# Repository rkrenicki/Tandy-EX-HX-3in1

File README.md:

# Tandy 1000 EX/HX 3-in-1 Expansion Board

This is a single expansion board designed for the Tandy 1000 EX and HX computers, to include the following upgrades:

* 640KB Base System Memory
* 96KB Upper Memory
* 16550-based DE9 Serial RS232 Port
* XT-IDE based CompactFlash "Hard Drive"

## Prerequisites

This board is for the Tandy 1000EX and 1000HX computers only.  It will not work in any other computer model as it is.
You must remove any expansion cards already in the computer, this is designed to be a single-board upgrade and has no provisions to allow for any other expansion cards.

## Installing

This board plugs into the Tandy PLUS interface, and takes up "Slot 2" on the rear of the computer.  Please be careful to align the PLUS bus connector before pushing down, to avoid bending pins on the computer.  Secure the backplate to the computer with two screws.
The IDE BIOS will automatically start and boot directly to the CF card on 1000EX machines.   1000HX loads a boot menu by default, and you will need to press F4 to load the IDE BIOS.  If you want to bypass the Tandy DOS ROM and boot menu, run "SETUPHX" and change the "Primary Start-up Device" to "DISK" and press F1 to save.

## Technical Details

This board has no configuration jumpers and is designed to be plug-and-play.  The only jumper is to enable programming the ROM.  Install the jumper to flash the XT-IDE BIOS, otherwise the jumper should be removed.  All assembled boards and kits sold by me come with a pre-programmed ROM, and this jumper should be left empty.

The board is hardwired with these memory locations/ports:
```
SRAM:  0x0000-0x5FFF, 0xC800-0xDFFF
UART:  0x3F8, IRQ 4
IDE:   0x300
ROM:   0xC000-0xC7FF
```

## Assembly Notes
All functions of the board are independent, no parts are shared between functions.  If you do not want to use a specific function, you can safely omit any parts referenced with the function in the name (such as "232" for RS232).

Recommended assembly order: (Shortest to tallest)
* 1  - Resistors (R1-R3, R4 for v1.8+)
* 2  - Bypass Capacitors (C1-C16, only noted as "0.1uF" on the boards)
* 3  - 74 series Chips (U1-4, U6-7, U9, U11-13)
* 4  - ROM Socket (U5 Socket)
* 5  - SRAM Chip (U10)
* 6  - Oscillator (OSC1)
* 7  - UART Socket (U8 Socket)  - Pay very special attention to the orientation!  See note below.
* 8  - Connectors (BUS1, CF-J1, CF-J2, 232-P2)
* 9 -  ROM and UART chips into their sockets.
* 10 - CF Adapter 
* 11 - Backplate 

NOTE:  Please take careful note of part orientation.  To optimize some trace routing, not all chips are oriented in the same direction.  232-U6, 232-U8, and RAM-U11 are all opposite oritentation than the other horizontal chips.  Installing these backwards will destroy the chips.   Pay special attention to 232-U8's socket, it must be installed with the "Pin 1 Arrow" installed facing towards the left of the board.  232-OSC1 is installed "upside down", with the squared corner facing the upper right.

## Bill of Materials
|Quantity |Ref(s)        |Mouser Part Number  |Digikey Part Number |Description                                                     
|-----|--------------|--------------------|--------------------|----------------------------------------------------------------
| 1   |BUS1          |200-CES13101SD<br><i><b>See Note2 Below</i>|SAM1084-31-ND<br><i><b>See Note2 Below</i>|2x31 2.54mm Header Socket
| 1   |CF-J1         |517-8540-4500PL     |MSPV40-ND               |2x20 2.54mm Header Socket, 11mm height.
| 4   |R1 through R4 |603-CFR-12JT-52-10K |13-CFR-12JT-52-10KCT-ND |10kOhm Resistor, 1/10w or 1/8w
| 16  |C1 through C16|594-K104M15X7RF53L2 |BC5142-ND               |0.1uF Multilayer Ceramic Capacitor, 2.5mm Lead Spacing
| 1   |CP1           |647-RNU1C101MDS1    |493-16276-ND            |47-100uF 6.3-16V Polymer or Electrolytic Capacitor, 2.5mm Lead Spacing
| 1   |232-OSC1      |774-MXO45HS-3C-1.8  |110-MXO45HS-3C-1M843200-ND |1.8432Mhz 1/2-size Oscillator
| 1   |232-P2        |806-K22X-E9P-N-99   |2092-K22X-E9P-N-ND      |DE9 Male Right Angle Connector  
| 2   |232-P2 Screw  |571-5207953-3       |SFSO4401NR-ND           |Jackscrew for DE9 connector
| 1   |232-U6        |595-GD75232N        |296-GD75232N-ND         |GD75232N RS232 Driver
| 2   |232-U7, 232-U9|595-SN74LS138N      |296-1639-5-ND           |74LS138 3-to-8 Line Demux
| 1   |232-U8        |701-ST16C550CJ44TR-F|1016-1259-5-ND          |16550/16C550 UART in PLCC-44 Package 
| 1   |232-U8 Socket |517-8444-11B1-RK-TP |3M4411B1-ND             |PLCC-44 Through Hole Socket
| 1   |CF-J2         |200-CES10101TD      |SAM1086-01-ND           |1x2 2.54mm Header Socket
| 1   |CF-U1         |595-SN74LS139AN     |296-1640-5-ND           |74LS139 Dual 2-to-4 Demux
| 2   |CF-U2, ROM-U4 |595-SN74LS688N<br> or 595-SN74F521N|296-1667-5-ND|74LS688 or 74F521 8-bit Comparator
| 2   |CF-U3, RAM-U11|595-SN74LS245N      |296-1655-5-ND           |74LS245 Tri-state Bus Transciever
| 1   |RAM-U10       |913-AS6C4008-55PCN  |1450-1027-ND            |AS6C4008-55PCN 4mbit (512k x 8) Static RAM
| 1   |RAM-U12       |595-SN74LS00N       |296-1626-ND             |74LS00 Quad NAND Gate
| 1   |RAM-U13       |595-SN74LS32N       |296-1658-5-ND           |74LS32 Quad OR Gate
| 1   |ROM-U5        |556-AT28C64B15PU    |AT28C64B-15PU-ND        |28C64 64k x 8 EEPROM
| 1   |ROM-U5 Socket |517-4828-6000-CP    |ED3052-5-ND             |28-pin Wide DIP Socket
| 1   |CF-IDE Adapter|n/a                 |n/a                     |CF to IDE Adapter from eBay or AliExpress (See note below)
| 1   |J1            |534-7327            |36-7327-ND              |Mounting Tab for Backplate

Note:	All 74LSxx series logic ICs can be substituted with any family with "LS" or "T" in the name, such as ALS, ACT, AHCT, or HCT among others.

Note2: For the BUS1 Connectors, I have many of these left over from my last order of custom connectors.   You can buy them from me for $1/ea plus shipping.  Even for one, it is far cheaper than the $13 that Mouser wants.   
For small quantities (1-20 connectors), visit my Tindie store to order:  https://www.tindie.com/products/rkrenicki/tandy-1000-ex-and-hx-bus-connector/
For larger quantities, please email tandy.3in1@gmail.com.
## BIOS

This board uses the XT-IDE Universal BIOS.  I have included pre-configured images for 2.0.0B3 r602 (latest version as of the time of writing this).  The 3in1BIOS-8088.zip will work on any EX or HX computer, and is the version that I preload on assembled boards and kits.   I have also included a V20 Enhanced version for any EX/HX that has an NEC V20 (or clone) installed.   This enhanced version will roughly double your disk speed, but only works on V20 machines.

## CF-IDE Adapter

This board is designed a specific version of a CF-IDE adapter.  They are widely available on eBay and AliExpress.  It bears the mark of "IDE to CF Ver.D2".  It can generally be identified by the metal cover over the CF card connector.   I do not have a link to any one specific vendor or listing, but if the adapter includes the metal backplate and has a metal cover over the CF slot, then it should be correct. 

The CF adapter does also need a few modifications, please refer to "PDFs\IDE Adapter Modifications.pdf" for details.  It also has photos of the adapter for reference to buy the proper adapter.  The backplate also has provisions for a mounting tab, please follow the directions found in "PDFs\Backplate Directions.pdf"

If you have any questions, feel free to join the Discord server below and ask in the #tandy-3in1-support channel.

## Support Discord

I have started a Discord server for more real-time technical support, as well as discussion for my various projects in progress.   You can follow this link to join:  https://discord.gg/QmFssyXnQt

## Built With

* [KiCAD EDA](http://www.kicad.org/)

## Authors

* **Rob Krenicki** - [rkrenicki](https://github.com/rkrenicki)

## License

This project is licensed under the Creative Commons - Attribution - ShareAlike 3.0 License

## Attribution

This board was derrived from works by, uses design elements from, or contains sofware writen by the following:
* Sergey Kiselev (http://www.malinov.com/Home/sergeys-projects)
* James Pearce (https://www.lo-tech.co.uk/)
* Adrian Black (https://www.youtube.com/user/craig1black/featured)
* Jacob Dorne of Monotech PCs (https://monotech.fwscart.com/)
* XTIDE Universal BIOS Team (http://www.xtideuniversalbios.org/)

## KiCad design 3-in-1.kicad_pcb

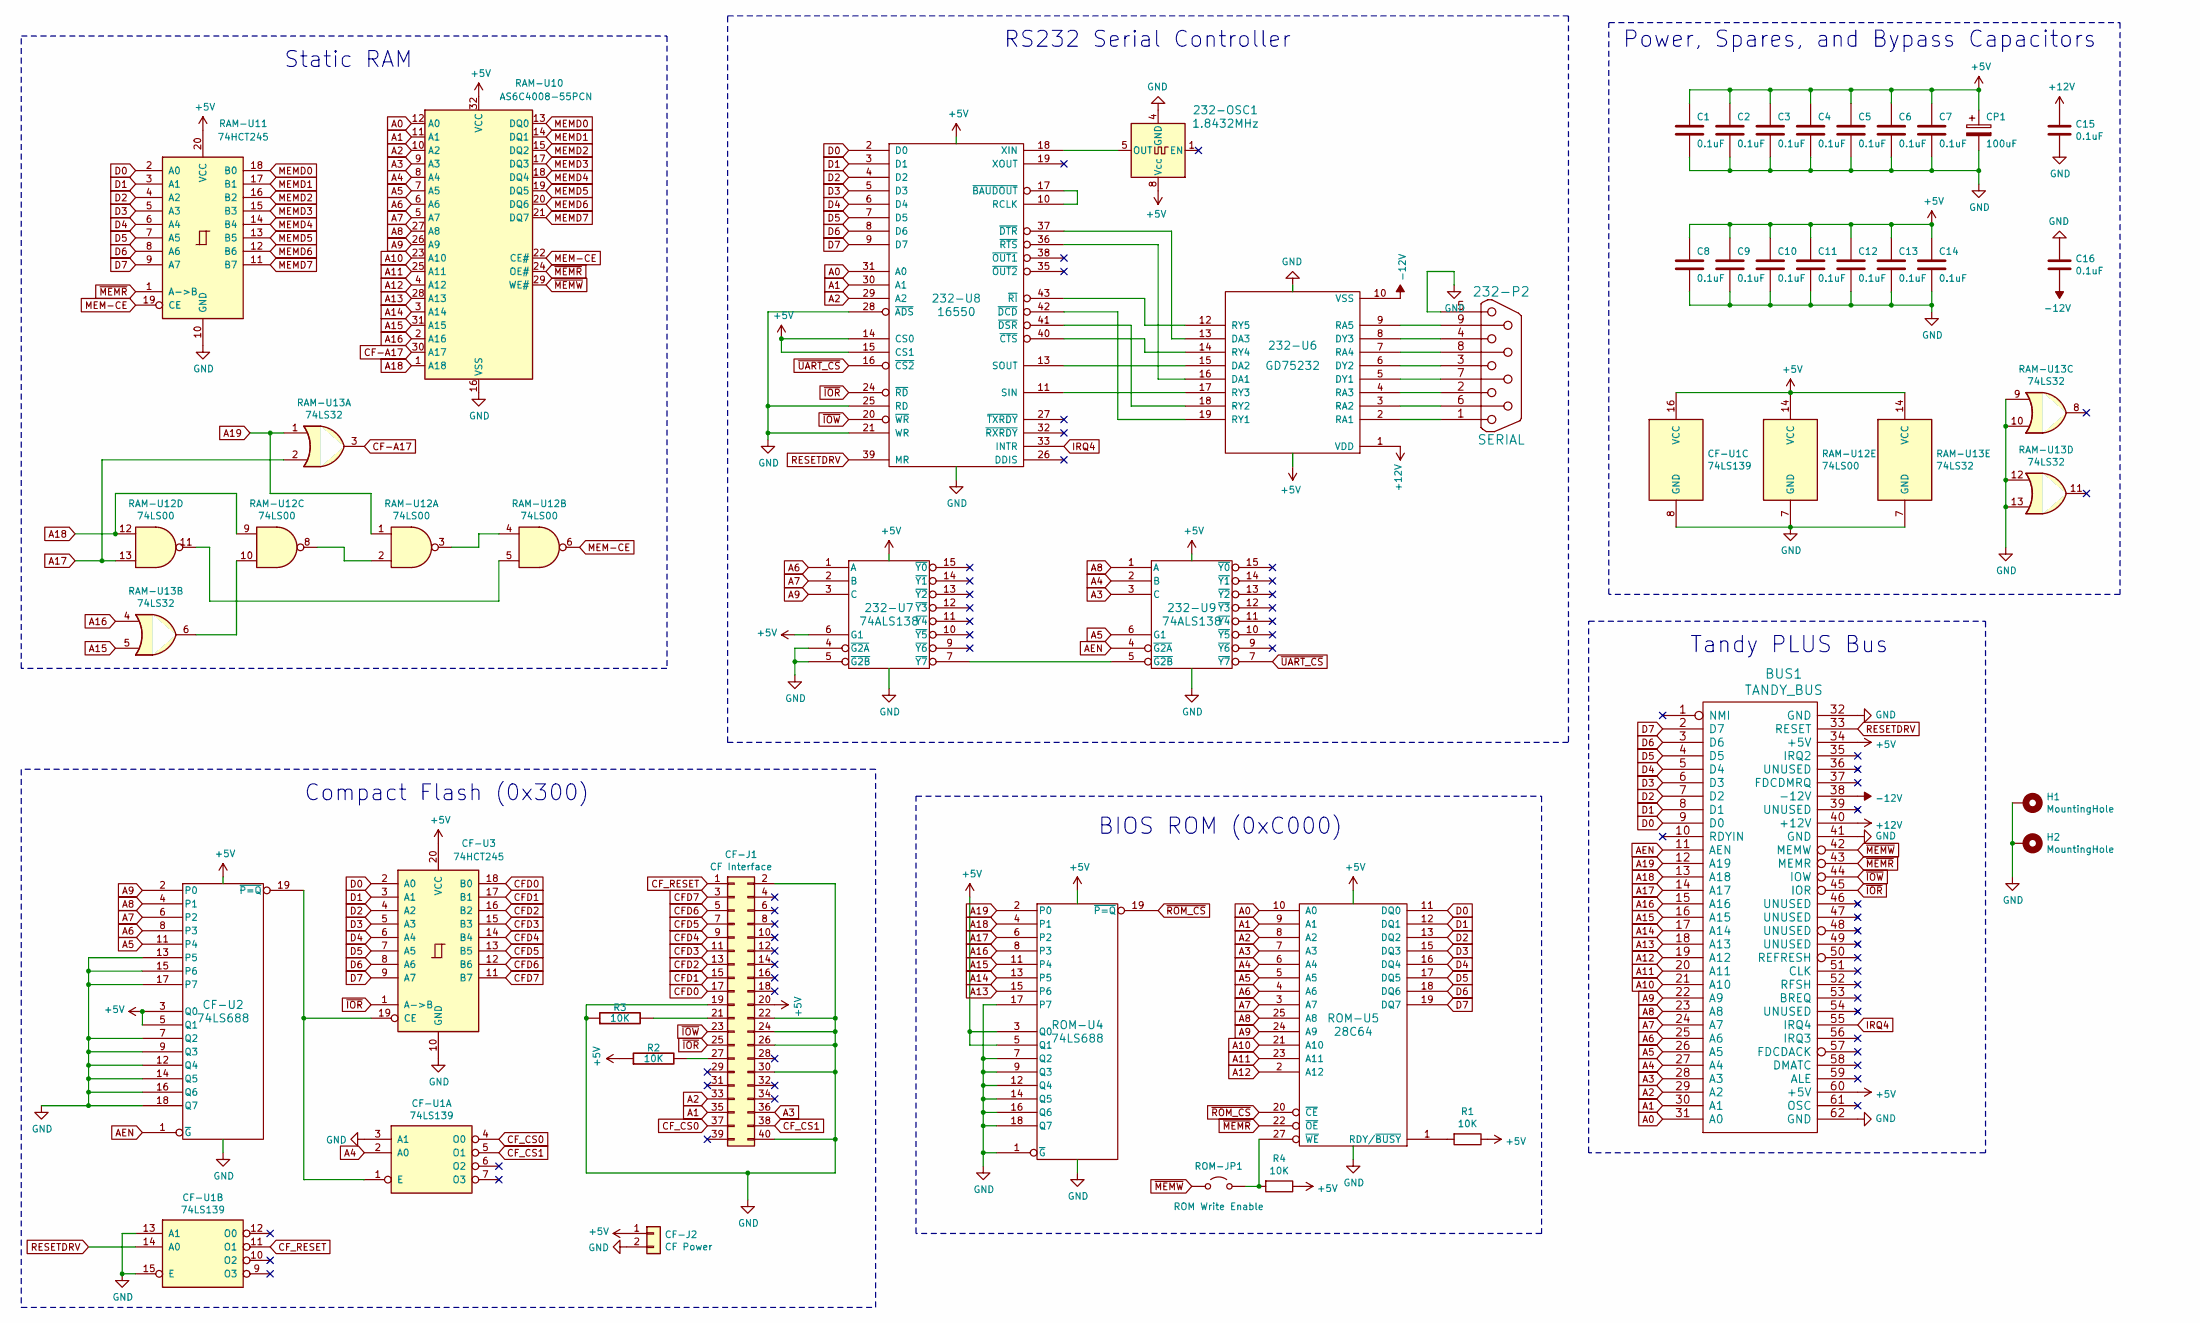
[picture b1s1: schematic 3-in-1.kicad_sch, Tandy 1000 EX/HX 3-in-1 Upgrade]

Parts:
232-OSC1: 1.8432MHz; Oscillator_DIP-8
232-P2: SERIAL; DSUB-9_Male_Horizontal_P2.77x2.84mm_EdgePinOffset7.70mm_Hou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
232-U6: GD75232; DIP-20_W7.62mm
232-U7, 232-U9: 74ALS138; DIP-16_W7.62mm
232-U8: 16550; PLCC-44_THT-Socket
BUS1: TANDY_BUS; TANDY-PLUS-BUS
C1, C2, C3, C4, C5, C6, C7, C8, C9, C10, C11, C12, C13, C14, C15, C16: 0.1uF; C_Disc_D3.0mm_W2.0mm_P2.50mm
CF-J1: CF Interface; PinSocket_2x20_P2.54mm_Vertical
CF-J2: CF Power; PinSocket_1x02_P2.54mm_Vertical
CF-U1: 74LS139; DIP-16_W7.62mm
CF-U2: 74LS688; DIP-20_W7.62mm
CF-U3: 74HCT245; DIP-20_W7.62mm
CP1: 100uF; CP_Radial_D5.0mm_P2.50mm
H1, H2: MountingHole; MountingHole_2.7mm_M2.5_ISO7380_Pad
R1, R2, R3, R4: 10K; R_Axial_DIN0204_L3.6mm_D1.6mm_P5.08mm_Horizontal
RAM-U10: AS6C4008-55PCN; DIP-32_W15.24mm
RAM-U11: 74HCT245; DIP-20_W7.62mm
RAM-U12: 74LS00; DIP-14_W7.62mm
RAM-U13: 74LS32; DIP-14_W7.62mm
ROM-JP1: ROM Write Enable; PinHeader_1x02_P2.54mm_Vertical
ROM-U4: 74LS688; DIP-20_W7.62mm
ROM-U5: 28C64; DIP-28_W15.24mm

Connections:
+5V: 232-OSC1.8 (Vcc), 232-U6.20 (VCC), 232-U7.6 (G1), 232-U7.16 (VCC), 232-U8.14 (CS0), 232-U8.15 (CS1), 232-U8.44 (VCC), 232-U9.16 (VCC), BUS1.34 (+5V), BUS1.60 (+5V), C1.1, C2.1, C3.1, C4.1, C5.1, C6.1, C7.1, C8.1, C9.1, C10.1, C11.1, C12.1, C13.1, C14.1, CF-J1.20, CF-J2.1, CF-U1.16 (VCC), CF-U2.3 (Q0), CF-U2.5 (Q1), CF-U2.20 (VCC), CF-U3.20 (VCC), CP1.1, R1.1, R2.1, R4.1, RAM-U10.32 (VCC), RAM-U11.20 (VCC), RAM-U12.14 (VCC), RAM-U13.14 (VCC), ROM-U4.3 (Q0), ROM-U4.5 (Q1), ROM-U4.20 (VCC), ROM-U5.28 (VCC)
+12V: 232-U6.1 (VDD), BUS1.40 (+12V), C15.1
-12V: 232-U6.10 (VSS), BUS1.38 (-12V), C16.2
A0: 232-U8.31 (A0), BUS1.31 (A0), RAM-U10.12 (A0), ROM-U5.10 (A0)
A1: 232-U8.30 (A1), BUS1.30 (A1), CF-J1.35, RAM-U10.11 (A1), ROM-U5.9 (A1)
A2: 232-U8.29 (A2), BUS1.29 (A2), CF-J1.33, RAM-U10.10 (A2), ROM-U5.8 (A2)
A3: 232-U9.3 (C), BUS1.28 (A3), CF-J1.36, RAM-U10.9 (A3), ROM-U5.7 (A3)
A4: 232-U9.2 (B), BUS1.27 (A4), CF-U1.2 (A0), RAM-U10.8 (A4), ROM-U5.6 (A4)
A5: 232-U9.6 (G1), BUS1.26 (A5), CF-U2.11 (P4), RAM-U10.7 (A5), ROM-U5.5 (A5)
A6: 232-U7.1 (A), BUS1.25 (A6), CF-U2.8 (P3), RAM-U10.6 (A6), ROM-U5.4 (A6)
A7: 232-U7.2 (B), BUS1.24 (A7), CF-U2.6 (P2), RAM-U10.5 (A7), ROM-U5.3 (A7)
A8: 232-U9.1 (A), BUS1.23 (A8), CF-U2.4 (P1), RAM-U10.27 (A8), ROM-U5.25 (A8)
A9: 232-U7.3 (C), BUS1.22 (A9), CF-U2.2 (P0), RAM-U10.26 (A9), ROM-U5.24 (A9)
A10: BUS1.21 (A10), RAM-U10.23 (A10), ROM-U5.21 (A10)
A11: BUS1.20 (A11), RAM-U10.25 (A11), ROM-U5.23 (A11)
A12: BUS1.19 (A12), RAM-U10.4 (A12), ROM-U5.2 (A12)
A13: BUS1.18 (A13), RAM-U10.28 (A13), ROM-U4.15 (P6)
A14: BUS1.17 (A14), RAM-U10.3 (A14), ROM-U4.13 (P5)
A15: BUS1.16 (A15), RAM-U10.31 (A15), RAM-U13.5, ROM-U4.11 (P4)
A16: BUS1.15 (A16), RAM-U10.2 (A16), RAM-U13.4, ROM-U4.8 (P3)
A17: BUS1.14 (A17), RAM-U12.13, RAM-U13.2, ROM-U4.6 (P2)
A18: BUS1.13 (A18), RAM-U10.1 (A18), RAM-U12.9, RAM-U12.12, ROM-U4.4 (P1)
A19: BUS1.12 (A19), RAM-U12.1, RAM-U13.1, ROM-U4.2 (P0)
AEN: 232-U9.4 (~G2A), BUS1.11 (AEN), CF-U2.1 (~G)
CF-A17: RAM-U10.30 (A17), RAM-U13.3
CFD0: CF-J1.17, CF-U3.18 (B0)
CFD1: CF-J1.15, CF-U3.17 (B1)
CFD2: CF-J1.13, CF-U3.16 (B2)
CFD3: CF-J1.11, CF-U3.15 (B3)
CFD4: CF-J1.9, CF-U3.14 (B4)
CFD5: CF-J1.7, CF-U3.13 (B5)
CFD6: CF-J1.5, CF-U3.12 (B6)
CFD7: CF-J1.3, CF-U3.11 (B7)
CF_CS0: CF-J1.37, CF-U1.4 (O0)
CF_CS1: CF-J1.38, CF-U1.5 (O1)
CF_RESET: CF-J1.1, CF-U1.11 (O1)
D0: 232-U8.2 (D0), BUS1.9 (D0), CF-U3.2 (A0), RAM-U11.2 (A0), ROM-U5.11 (DQ0)
D1: 232-U8.3 (D1), BUS1.8 (D1), CF-U3.3 (A1), RAM-U11.3 (A1), ROM-U5.12 (DQ1)
D2: 232-U8.4 (D2), BUS1.7 (D2), CF-U3.4 (A2), RAM-U11.4 (A2), ROM-U5.13 (DQ2)
D3: 232-U8.5 (D3), BUS1.6 (D3), CF-U3.5 (A3), RAM-U11.5 (A3), ROM-U5.15 (DQ3)
D4: 232-U8.6 (D4), BUS1.5 (D4), CF-U3.6 (A4), RAM-U11.6 (A4), ROM-U5.16 (DQ4)
D5: 232-U8.7 (D5), BUS1.4 (D5), CF-U3.7 (A5), RAM-U11.7 (A5), ROM-U5.17 (DQ5)
D6: 232-U8.8 (D6), BUS1.3 (D6), CF-U3.8 (A6), RAM-U11.8 (A6), ROM-U5.18 (DQ6)
D7: 232-U8.9 (D7), BUS1.2 (D7), CF-U3.9 (A7), RAM-U11.9 (A7), ROM-U5.19 (DQ7)
GND: 232-OSC1.4 (GND), 232-P2.0, 232-P2.5, 232-U6.11 (GND), 232-U7.4 (~G2A), 232-U7.5 (~G2B), 232-U7.8 (GND), 232-U8.21 (WR), 232-U8.22 (GND), 232-U8.25 (RD), 232-U8.28 (~ADS), 232-U9.8 (GND), BUS1.32 (GND), BUS1.41 (GND), BUS1.62 (GND), C1.2, C2.2, C3.2, C4.2, C5.2, C6.2, C7.2, C8.2, C9.2, C10.2, C11.2, C12.2, C13.2, C14.2, C15.2, C16.1, CF-J1.2, CF-J1.19, CF-J1.22, CF-J1.24, CF-J1.26, CF-J1.30, CF-J1.40, CF-J2.2, CF-U1.3 (A1), CF-U1.8 (GND), CF-U1.13 (A1), CF-U1.15 (E), CF-U2.7 (Q2), CF-U2.9 (Q3), CF-U2.10 (GND), CF-U2.12 (Q4), CF-U2.13 (P5), CF-U2.14 (Q5), CF-U2.15 (P6), CF-U2.16 (Q6), CF-U2.17 (P7), CF-U2.18 (Q7), CF-U3.10 (GND), CP1.2, H1.1, H2.1, R3.1, RAM-U10.16 (VSS), RAM-U11.10 (GND), RAM-U12.7 (GND), RAM-U13.7 (GND), RAM-U13.9, RAM-U13.10, RAM-U13.12, RAM-U13.13, ROM-U4.1 (~G), ROM-U4.7 (Q2), ROM-U4.9 (Q3), ROM-U4.10 (GND), ROM-U4.12 (Q4), ROM-U4.14 (Q5), ROM-U4.16 (Q6), ROM-U4.17 (P7), ROM-U4.18 (Q7), ROM-U5.14 (GND)
IRQ4: 232-U8.33 (INTR), BUS1.55 (IRQ4)
MEM-CE: RAM-U10.22 (CE#), RAM-U11.19 (CE), RAM-U12.6
MEMD0: RAM-U10.13 (DQ0), RAM-U11.18 (B0)
MEMD1: RAM-U10.14 (DQ1), RAM-U11.17 (B1)
MEMD2: RAM-U10.15 (DQ2), RAM-U11.16 (B2)
MEMD3: RAM-U10.17 (DQ3), RAM-U11.15 (B3)
MEMD4: RAM-U10.18 (DQ4), RAM-U11.14 (B4)
MEMD5: RAM-U10.19 (DQ5), RAM-U11.13 (B5)
MEMD6: RAM-U10.20 (DQ6), RAM-U11.12 (B6)
MEMD7: RAM-U10.21 (DQ7), RAM-U11.11 (B7)
unnamed: 232-OSC1.5 (OUT), 232-U8.18 (XIN)
unnamed: 232-P2.1, 232-U6.2 (RA1)
unnamed: 232-P2.2, 232-U6.4 (RA3)
unnamed: 232-P2.3, 232-U6.6 (DY2)
unnamed: 232-P2.4, 232-U6.8 (DY3)
unnamed: 232-P2.6, 232-U6.3 (RA2)
unnamed: 232-P2.7, 232-U6.5 (DY1)
unnamed: 232-P2.8, 232-U6.7 (RA4)
unnamed: 232-P2.9, 232-U6.9 (RA5)
unnamed: 232-U6.12 (RY5), 232-U8.43 (~RI)
unnamed: 232-U6.13 (DA3), 232-U8.37 (~DTR)
unnamed: 232-U6.14 (RY4), 232-U8.40 (~CTS)
unnamed: 232-U6.15 (DA2), 232-U8.13 (SOUT)
unnamed: 232-U6.16 (DA1), 232-U8.36 (~RTS)
unnamed: 232-U6.17 (RY3), 232-U8.11 (SIN)
unnamed: 232-U6.18 (RY2), 232-U8.41 (~DSR)
unnamed: 232-U6.19 (RY1), 232-U8.42 (~DCD)
unnamed: 232-U7.7 (~Y7), 232-U9.5 (~G2B)
unnamed: 232-U8.10 (RCLK), 232-U8.17 (~BAUDOUT)
unnamed: CF-J1.21, R3.2
unnamed: CF-J1.27, R2.2
unnamed: CF-U1.1 (E), CF-U2.19 (~P=Q), CF-U3.19 (CE)
unnamed: R1.2, ROM-U5.1 (RDY/~BUSY)
unnamed: R4.2, ROM-JP1.2 (B), ROM-U5.27 (~WE)
unnamed: RAM-U12.2, RAM-U12.8
unnamed: RAM-U12.3, RAM-U12.4
unnamed: RAM-U12.10, RAM-U13.6
unnamed: RAM-U12.5, RAM-U12.11
RESETDRV: 232-U8.39 (MR), BUS1.33 (RESET), CF-U1.14 (A0)
~IOR: 232-U8.24 (~RD), BUS1.45 (IOR), CF-J1.25, CF-U3.1 (A->B)
~IOW: 232-U8.20 (~WR), BUS1.44 (IOW), CF-J1.23
~MEMR: BUS1.43 (MEMR), RAM-U10.24 (OE#), RAM-U11.1 (A->B), ROM-U5.22 (~OE)
~MEMW: BUS1.42 (MEMW), RAM-U10.29 (WE#), ROM-JP1.1 (A)
~ROM_CS: ROM-U4.19 (~P=Q), ROM-U5.20 (~CE)
~UART_CS: 232-U8.16 (~CS2), 232-U9.7 (~Y7)

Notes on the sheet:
BIOS ROM (0xC000)
Power, Spares, and Bypass Capacitors
Static RAM
Tandy PLUS Bus
Compact Flash (0x300)
RS232 Serial Controller

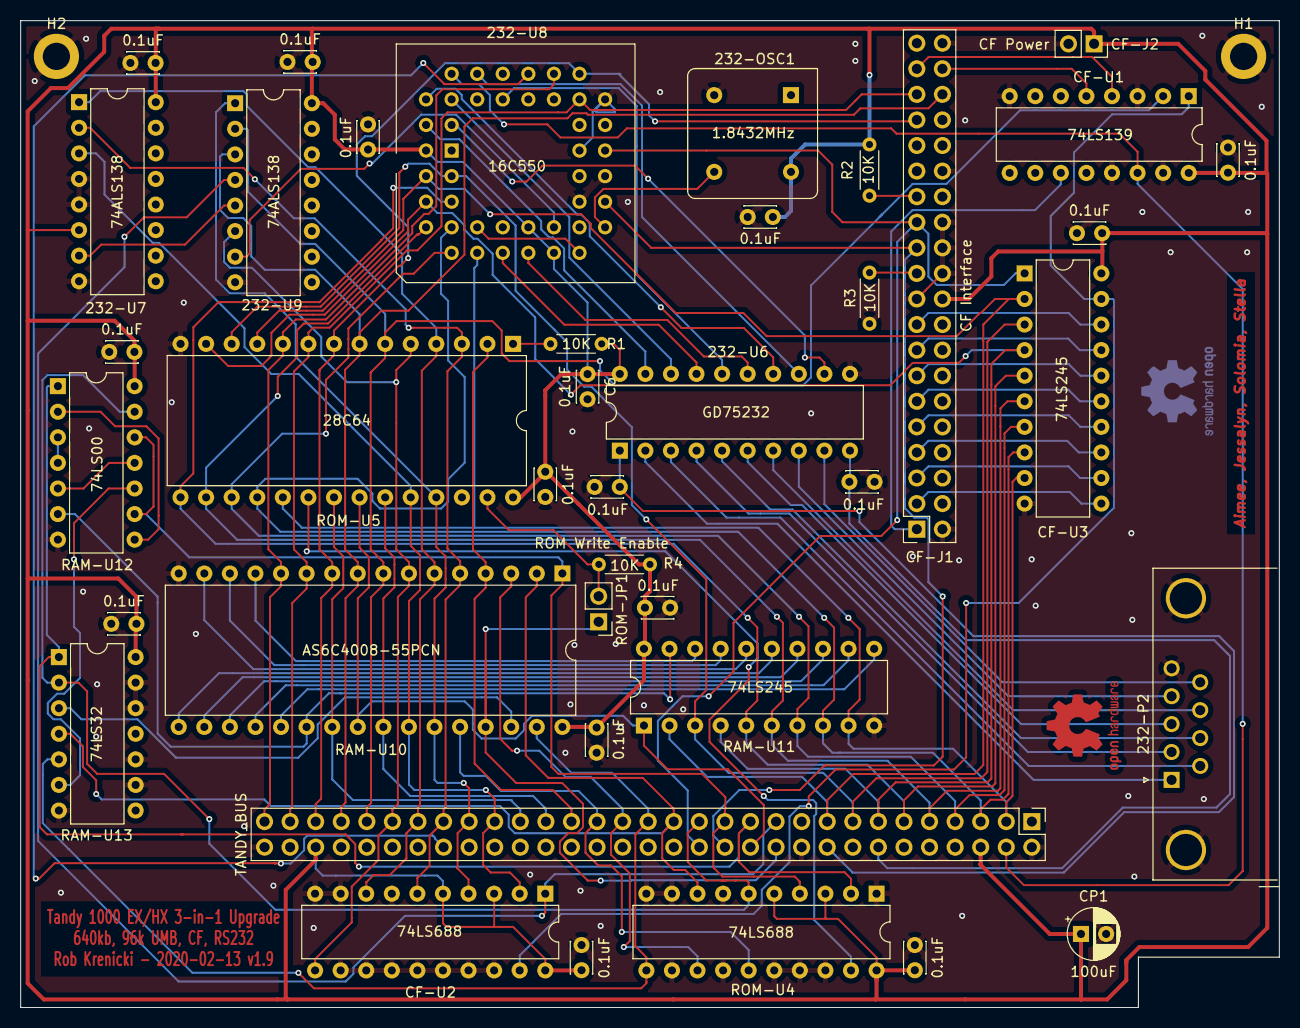
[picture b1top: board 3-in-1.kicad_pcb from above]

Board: 2 copper layers, 125.0 x 98.0 mm, 42 parts (0 on the bottom side), 90 nets.

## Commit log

2019-11-13 Readme Update
2019-11-13 Add UMB drivers
2019-11-13 Utilities Update
2019-11-18 Gerber update
2019-11-18 Silkscreen Update
2019-11-19 Layout cleanup
2019-11-21 v1.7a update
2019-11-24 Create LICENSE
2019-11-30 Pull-up Resistor added
2019-12-06 1.8 update
2019-12-16 Driver Update and Backplate
2020-01-09 Create 3in1bios.zip
    Preconfigured XT-IDE r602 BIOS Image
2020-01-09 Driver Updates
2020-01-13 Driver Update
2020-01-14 Disk Images
    Added floppy images, Deleted CF card image since it was not working for all cards.
2020-02-04 Adding PDF Schematic
2020-02-13 Addition of V20 enhanced BIOS.
2020-02-15 Version 1.9 Update
2020-05-06 Update README.md
    Update for F521
2021-01-21 Update README.md
    Fix Typo in BOM
2021-11-19 Initial Commit v1.9
2022-01-22 Update README.md
    Addition of Digikey Part Numbers
2022-07-21 Update README, Move PDFs to folder.
2025-11-08 Update to KiCAD 9

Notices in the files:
3-in-1.kicad_sch:
OSHW - Creative Commons Attribution ShareAlike 3.0
